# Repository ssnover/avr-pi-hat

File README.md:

# AVR Pi Hat
This is a small hardware project to build a daughterboard for the Raspberry Pi 3 which will house an Atmega328P microcontroller as a coprocessor, allowing UART communication between the boards and allowing the Raspberry Pi to flash new firmware to the AVR. Additionally the board will have the R3 headers common to Arduino and extend the Pi's headers to be available for prototyping.

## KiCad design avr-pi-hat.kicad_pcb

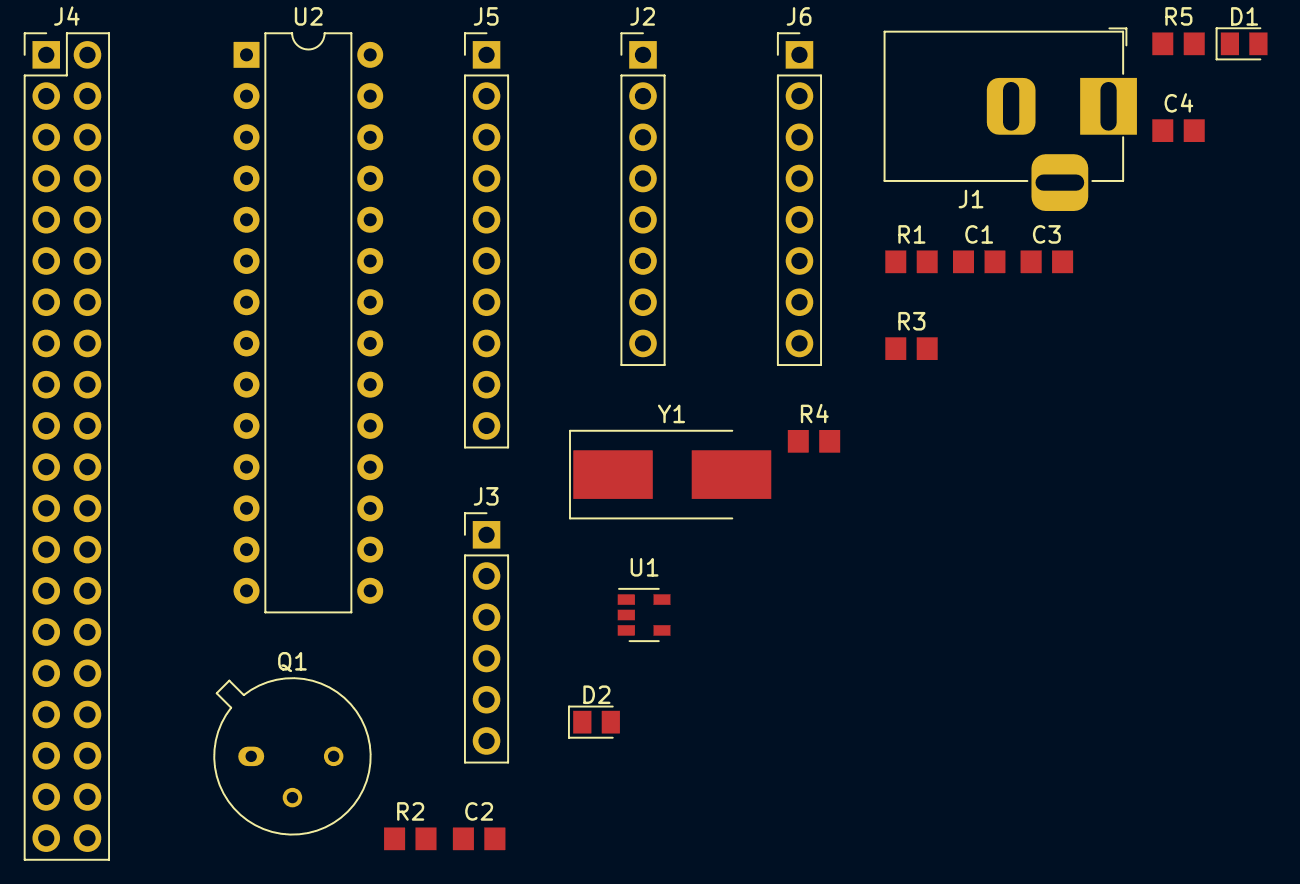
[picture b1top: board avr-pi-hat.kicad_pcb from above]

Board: 2 copper layers, 21 parts (0 on the bottom side), 30 nets, no tracks yet.

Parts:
C1: 1u; C_0805_2012Metric_Pad1.29x1.40mm_HandSolder
C2: 100n; C_0805_2012Metric_Pad1.29x1.40mm_HandSolder
C3, C4: 22p; C_0805_2012Metric_Pad1.29x1.40mm_HandSolder
D1, D2: LED; LED_0805_2012Metric_Pad1.12x1.40mm_HandSolder
J1: Barrel_Jack; BarrelJack_Horizontal
J2, J6: Conn_01x08; PinHeader_1x08_P2.54mm_Vertical
J3: Conn_01x06; PinHeader_1x06_P2.54mm_Vertical
J4: Conn_02x20_Odd_Even; PinHeader_2x20_P2.54mm_Vertical
J5: Conn_01x10; PinHeader_1x10_P2.54mm_Vertical
Q1: 2N2219; TO-39-3
R1, R2: 330; R_0805_2012Metric_Pad1.29x1.40mm_HandSolder
R3: 1M; R_0805_2012Metric_Pad1.29x1.40mm_HandSolder
R4: 100k; R_0805_2012Metric_Pad1.29x1.40mm_HandSolder
R5: 10k; R_0805_2012Metric_Pad1.29x1.40mm_HandSolder
U1: LP2985-3.3; SOT-23-5
U2: ATmega328-PU; DIP-28_W7.62mm
Y1: 16MHz; Crystal_SMD_7050-2Pin_7.0x5.0mm_HandSoldering

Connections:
3V3: C1.1, D2.2, J2.5, J4.1, U1.5
+5V: C2.1, D1.2, J2.4, J4.2, J4.4, R5.1, U1.1, U1.3, U2.7, U2.20
A0: J3.1, U2.23
A1: J3.2, U2.24
A2: J3.3, U2.25
A3: J3.4, U2.26
A4: J3.5, J5.9, U2.27
A5: J3.6, J5.10, U2.28
AREF: J5.8, U2.21
AVR_RST: J4.7, Q1.2, R4.1
D0: J4.8, J6.1, U2.2
D1: J4.10, J6.2, U2.3
D2: J6.3, U2.4
D3: J6.4, U2.5
D4: J6.5, U2.6
D5: J6.6, U2.11
D6: J6.7, U2.12
D7: J6.8, U2.13
D8: J5.1, U2.14
D9: J5.2, U2.15
D10: J5.3, U2.16
D11: J4.35, J5.4, U2.17
D12: J4.37, J5.5, U2.18
D13: J4.33, J5.6, U2.19
GND: C1.2, C2.2, C3.1, C4.1, J1.2, J1.3, J2.2, J2.3, J4.6, J5.7, Q1.1, R1.2, R2.2, R4.2, U1.2, U2.8, U2.22
unnamed: C3.2, R3.1, U2.9, Y1.1
unnamed: C4.2, R3.2, U2.10, Y1.2
unnamed: D1.1, R1.1
unnamed: D2.1, R2.1
~RESET: J2.6, J4.31, Q1.3, R5.2, U2.1

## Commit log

2018-06-03 Added Readme
2018-06-03 Removed extra reset circuitry, added level shifting to AVR TX
